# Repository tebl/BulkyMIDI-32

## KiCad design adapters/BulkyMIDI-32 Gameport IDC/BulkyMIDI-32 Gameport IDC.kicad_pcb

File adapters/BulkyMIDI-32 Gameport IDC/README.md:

# BulkyMIDI-32 Gameport (IDC)
This is an alternative version of [BulkyMIDI-32 Gameport](https://github.com/tebl/BulkyMIDI-32/tree/main/BulkyMIDI-32%20Gameport), the difference is that instead of a right-angle DB15 connector we've got an IDC connector. For more general information about what this adapter is and what it is, check out the documentation for the regular version.

Using a cable increases the cost of the unit slightly, as we'd need to buy the cable including any connectors not already on it (I've seen Uxcell-branded cables that are ready made on AliExpress and Ebay). Having the adapter on a cable means we've got the flexibility of using it mostly everywhere, primarily by not getting in the way of other inputs on the motherboard or sound card. The pinout should also match the same [pinout](https://www.frontx.com/cpx091_2.html) used on motherboard breakout cables (usually with pin 16 missing), so in theory you could use a 2x8 pin ribbon cable and connect it directly to motherboard that only has pin-headers in place of a gameport connector.

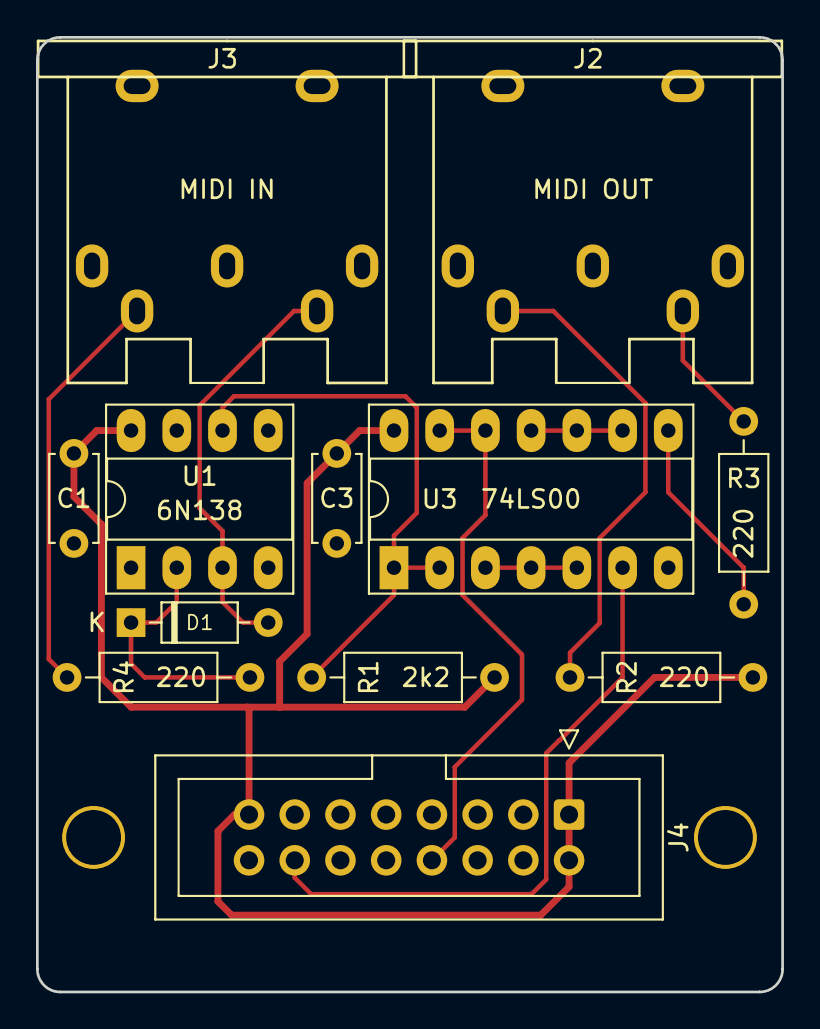
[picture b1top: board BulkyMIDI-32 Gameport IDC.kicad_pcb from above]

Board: 2 copper layers, 41.4 x 53.0 mm, 14 parts (0 on the bottom side), 13 nets.

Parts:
C1, C3: 100nF; C_Disc_D4.7mm_W2.5mm_P5.00mm
D1: 1N4148; D_DO-35_SOD27_P7.62mm_Horizontal
J2: MIDI OUT; DIN5_MIDI
J3: MIDI IN; DIN5_MIDI
J4: Gameport; Gameport_IDC
M1, M2: Mounting; M3
R1: 2k2; R_Axial_DIN0207_L6.3mm_D2.5mm_P10.16mm_Horizontal
R2, R3, R4: 220; R_Axial_DIN0207_L6.3mm_D2.5mm_P10.16mm_Horizontal
U1: 6N138; DIP-8_W7.62mm_Socket_LongPads
U3: 74LS00; DIP-14_W7.62mm_Socket_LongPads

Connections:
+5V: C1.1, C3.1, J4.1, J4.8, J4.9, R1.1, R2.1, U1.8, U3.14
GND: C1.2, C3.2, J2.2, J4.4, J4.5, U1.5, U3.7
MIDI_RxD: J4.15, U3.6
MIDI_TxD: J4.12, U3.12, U3.13
unnamed: D1.1, R4.1, U1.2
unnamed: D1.2, J3.5, U1.3
unnamed: J2.4, R2.2
unnamed: J2.5, R3.1
unnamed: J3.4, R4.2
unnamed: R1.2, U1.6, U3.1, U3.2
unnamed: R3.2, U3.8
unnamed: U3.3, U3.4, U3.5
unnamed: U3.9, U3.10, U3.11

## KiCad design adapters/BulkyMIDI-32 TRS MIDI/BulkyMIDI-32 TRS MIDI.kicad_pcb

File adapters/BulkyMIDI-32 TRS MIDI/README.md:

# BulkyMIDI-32 TRS MIDI
Working on the [BulkyMIDI-32 Internal](https://github.com/tebl/BulkyMIDI-32/tree/main/BulkyMIDI-32%20Internal) I made the choice of using TRS sockets for the MIDI-signals, thinking that was an easy way to get it connected up to my other equipment - as that would just require buying such a ready-made cable. Unfortunately though, the ones I had ordered up from China were simply wired up wrong - they were intended for audio and did not match any of the known pinouts for MIDI. I did order them up from a music store, but they've been delayed so many times that I just wanted *something* that I could rely on!

Myself. Meaning that I threw together this adapter, allowing me to use a standard 3.5mm stereo audio cable for MIDI-purposes. Yes I could probably have just ordered one from a really expensive store and have it delivered within a week from international site for professional musicians that know what they are doing, but I didn't like the fact that a short little cable - would somehow end up being the most expensive component when building an *MT32-PI*.

Helpfully enough, there are two competing standards for how such a thing should be wired - commonly referred to as *type A* and *type B*. [A simplified guide to MIDI over TRS minijacks](https://minimidi.world/) goes into all of the detail that you would ever need to understand for the both of them. In practice when it comes to the adapter that I made, there's a set of jumpers that need to be set according to the equipment you're using - either horizontal (*type A*) or vertical (*type B*).

- [1> Building the device](#1-building-the-device)
- [2> Schematic](#2-schematic)
- [3> BOM](#3-bom)

# 1> Building the device
Building the device should be a straight forward affair, you just solder the two components into place. Just don't burn yourself while doing so. Some 5-pin TRS socket types may have little plastic *"nubs"* underneath them that you may need to snip off to make it sit perfectly flush, but most will fit. 

# 2> Schematic
The supplied KiCad files should be sufficient as both a schematic and as a  starting point for ordering PCBs (basically you could just zip the contents of the export folder and upload that on a fabrication site), the schematic is also available in [PDF-format](https://github.com/tebl/BulkyMIDI-32/tree/main/documentation/schematic/adapters) and this is what you'll need to print and work your way through when things fail to work as expected.

# 3> BOM
Most parts should be easy to get a hold of from your favourite local electronic component shop, but given that I don't have access to such shops where I live so everything was based on whatever I could get cheapest from eBay/AliExpress (free shipping, but plan on waiting 3-4 weeks for delivery). 

| Reference      | Item                                                  | Count | Order  |
| ---------------| ----------------------------------------------------- | ----- | ------ |
| Faceplate PCB  | Fabricate using Gerber files                          |     1 | [PCBWay](https://www.pcbway.com/project/shareproject/MIDI_to_TRS_Adapter_fb57ed94.html)
| J1             | PJ-307 3.5mm socket (alternatively PJ-317)            |     1 |
| J2             | Female S-terminal 5pin DIN PCB                        |     1 |
| J3             | Straight pin headers, with two jumper caps            |     1 |
|                | 3.5mm TRS cable (M-M), preferably of decent quality   |     1 |

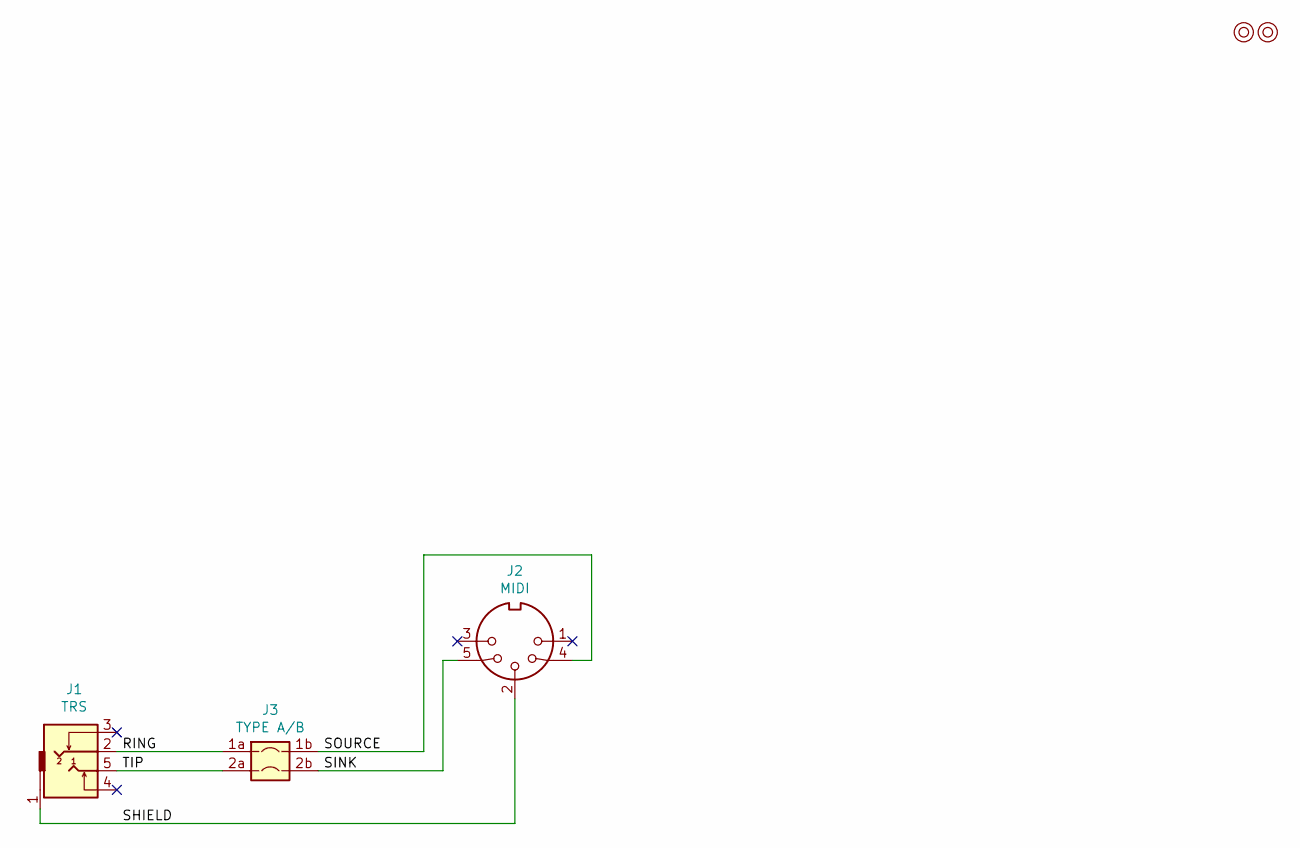
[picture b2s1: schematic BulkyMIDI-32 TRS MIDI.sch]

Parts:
J1: TRS; PJ-317
J2: MIDI; DIN5_MIDI_ANY
J3: TYPE A/B; select_swappable_THT
M1, M2: Mounting; M3

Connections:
/RING: J1.2, J3.1a
/SHIELD: J1.1, J2.2
/SINK: J2.5, J3.2b
/SOURCE: J2.4, J3.1b
/TIP: J1.5, J3.2a

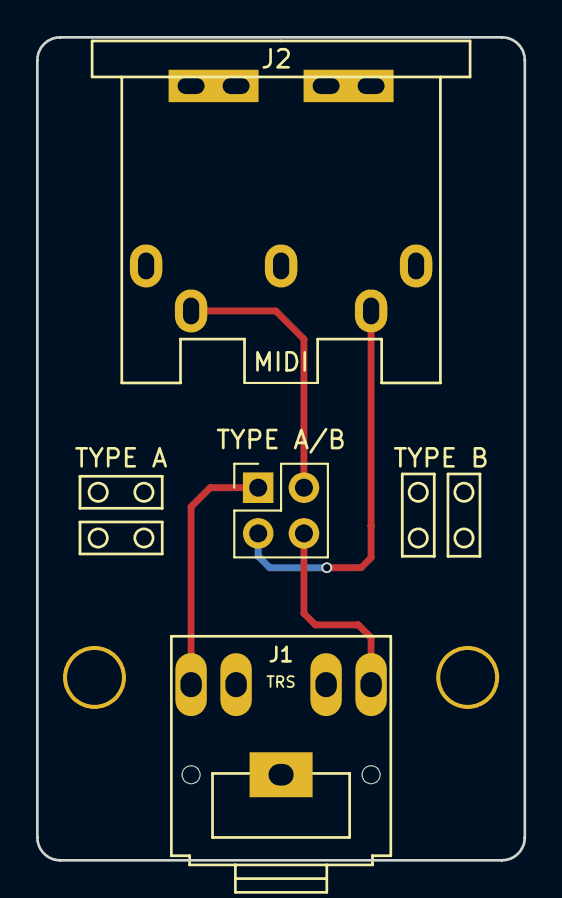
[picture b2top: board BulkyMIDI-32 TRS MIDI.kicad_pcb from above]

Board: 2 copper layers, 27.1 x 45.7 mm, 5 parts (0 on the bottom side), 5 nets.

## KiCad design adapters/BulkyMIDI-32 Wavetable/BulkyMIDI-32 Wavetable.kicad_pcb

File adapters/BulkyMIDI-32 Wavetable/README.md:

# BulkyMIDI-32 Wavetable
*UNTESTED*
While the MT32-PI already have quite a lot of options for connecting the device up to everyones favourite IBM PC/AT compatible computers, but I thought I'd put some efforts into making yet another one - this time attempting to fill the void on my **Sound Blaster 16** by having something to attach to the wavetable header.

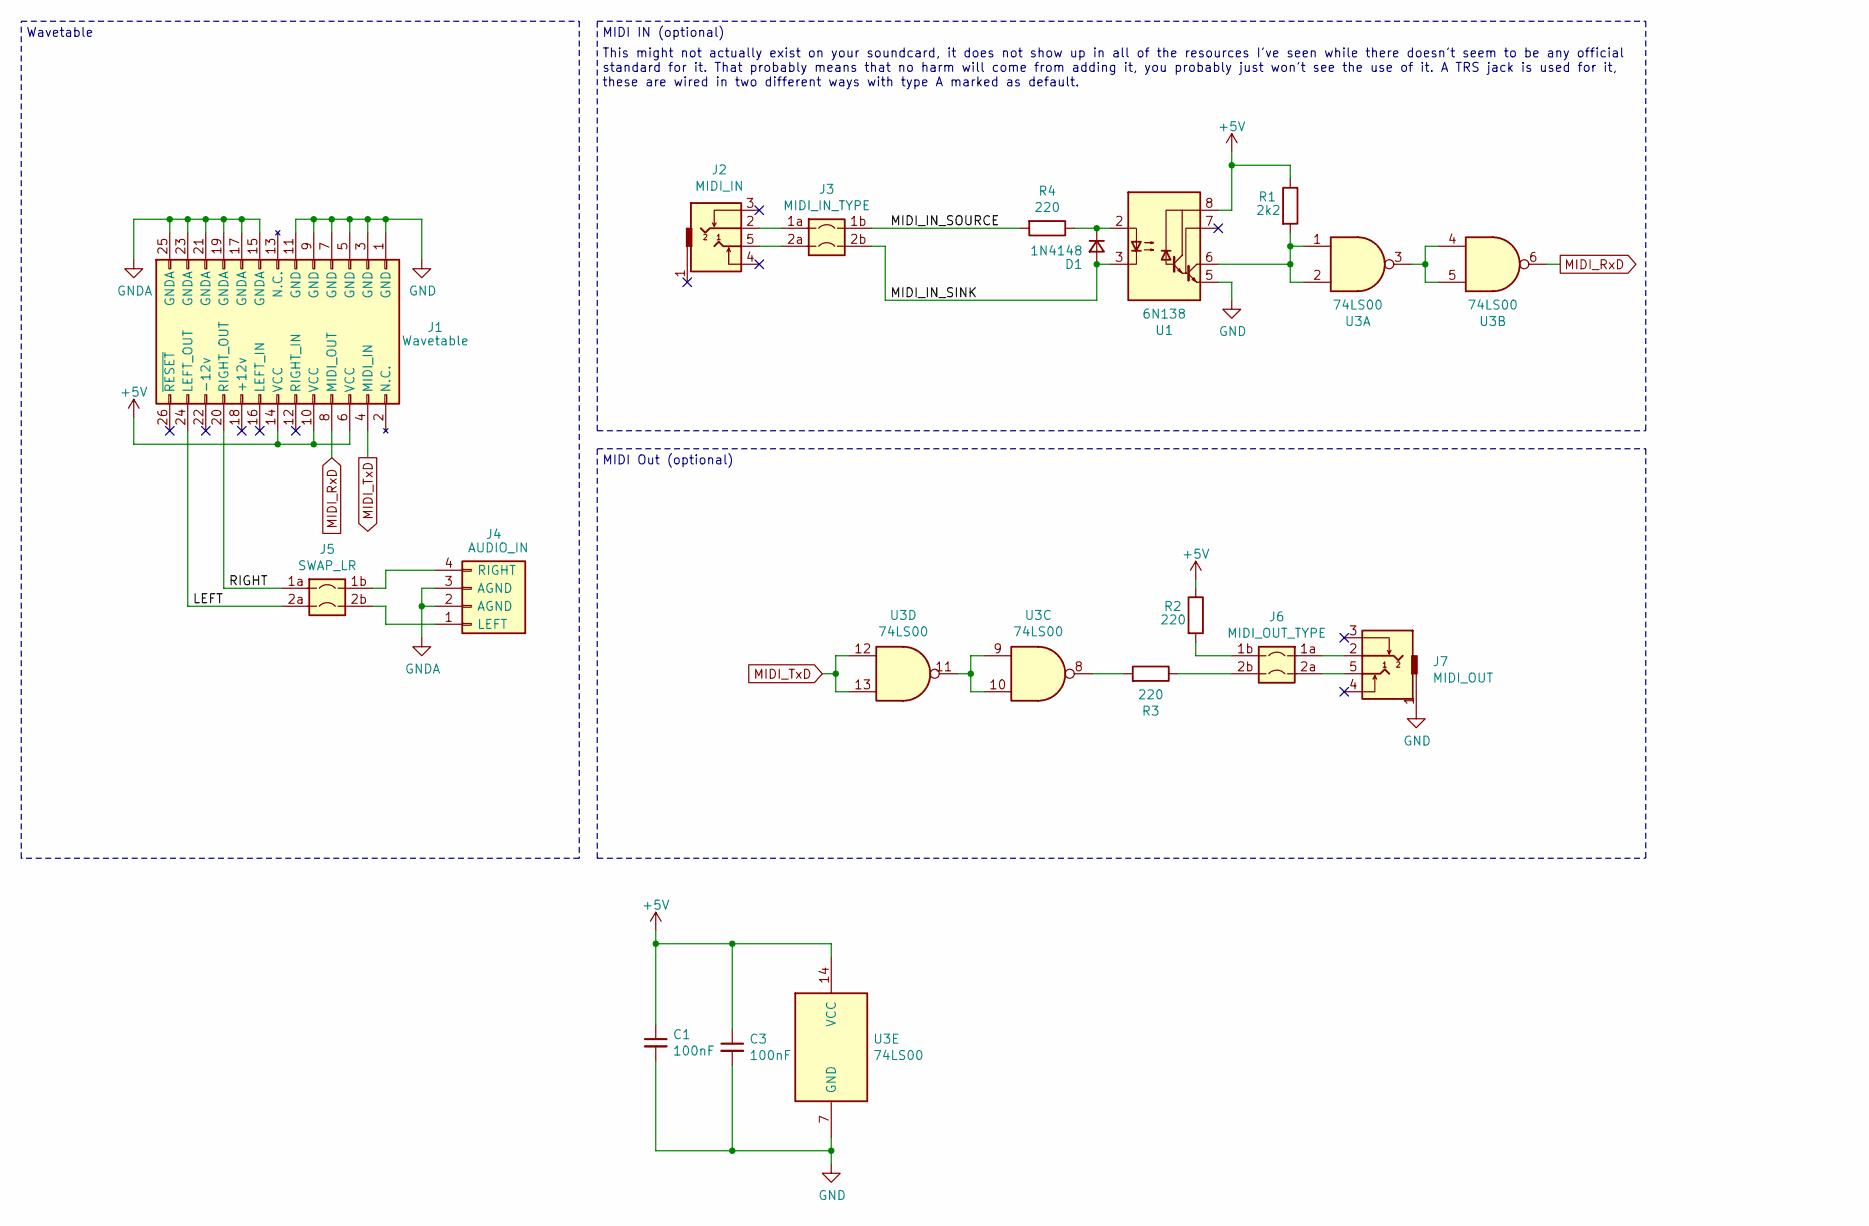
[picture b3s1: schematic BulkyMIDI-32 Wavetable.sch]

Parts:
C1, C3: 100nF; C_Disc_D4.7mm_W2.5mm_P5.00mm
D1: 1N4148; D_DO-35_SOD27_P7.62mm_Horizontal
J1: Wavetable
J2: MIDI_IN; PJ-317_IN
J3: MIDI_IN_TYPE; select_swappable
J4: AUDIO_IN; PinHeader_1x04_P2.54mm_Horizontal
J5: SWAP_LR; select_swappable
J6: MIDI_OUT_TYPE; select_swappable
J7: MIDI_OUT; PJ-317_OUT
R1: 2k2; R_Axial_DIN0207_L6.3mm_D2.5mm_P10.16mm_Horizontal
R2, R3, R4: 220; R_Axial_DIN0207_L6.3mm_D2.5mm_P10.16mm_Horizontal
U1: 6N138; DIP-8_W7.62mm_Socket_LongPads
U3: 74LS00; DIP-14_W7.62mm_Socket_LongPads

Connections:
+5V: C1.1, C3.1, J1.6 (VCC), J1.10 (VCC), J1.14 (VCC), R1.1, R2.1, U1.8 (VCC), U3.14 (VCC)
/LEFT: J1.24 (LEFT_OUT), J5.2a
/MIDI_IN_SINK: D1.2 (A), J3.2b, U1.3 (C2)
/MIDI_IN_SOURCE: J3.1b, R4.2
/RIGHT: J1.20 (RIGHT_OUT), J5.1a
GND: C1.2, C3.2, J1.1 (GND), J1.3 (GND), J1.5 (GND), J1.7 (GND), J1.9 (GND), J1.11 (GND), J7.1, U1.5 (GND), U3.7 (GND)
GNDA: J1.15 (GNDA), J1.17 (GNDA), J1.19 (GNDA), J1.21 (GNDA), J1.23 (GNDA), J1.25 (GNDA), J4.2 (AGND), J4.3 (AGND)
MIDI_RxD: J1.8 (MIDI_OUT), U3.6
MIDI_TxD: J1.4 (MIDI_IN), U3.12, U3.13
unnamed: D1.1 (K), R4.1, U1.2 (C1)
unnamed: J2.2, J3.1a
unnamed: J2.5, J3.2a
unnamed: J4.1 (LEFT), J5.2b
unnamed: J4.4 (RIGHT), J5.1b
unnamed: J6.1a, J7.2
unnamed: J6.1b, R2.2
unnamed: J6.2a, J7.5
unnamed: J6.2b, R3.1
unnamed: R1.2, U1.6 (VO2), U3.1, U3.2
unnamed: R3.2, U3.8
unnamed: U3.3, U3.4, U3.5
unnamed: U3.9, U3.10, U3.11

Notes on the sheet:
MIDI IN (optional)
MIDI Out (optional)
Wavetable
This might not actually exist on your soundcard, it does not show up in all of the resources I've seen while there doesn't seem to be any official standard for it. That probably means that no harm will come from adding it, you probably just won't see the use of it. A TRS jack is used for it, these 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

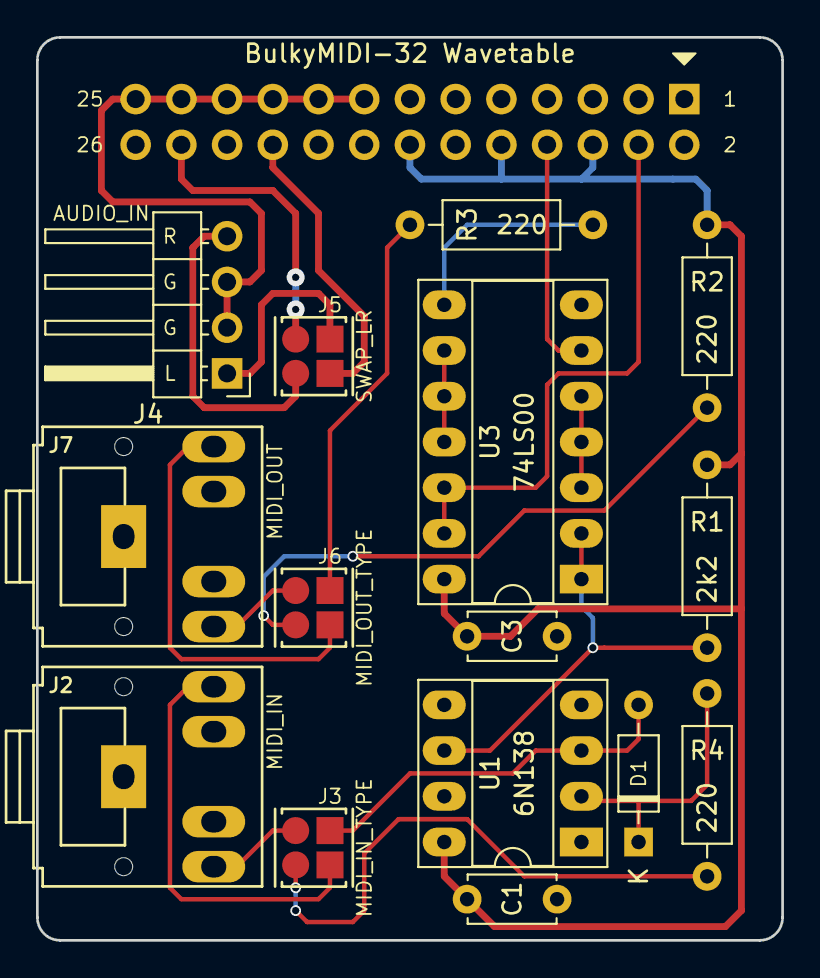
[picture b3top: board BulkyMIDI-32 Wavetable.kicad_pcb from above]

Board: 2 copper layers, 41.4 x 50.2 mm, 16 parts (0 on the bottom side), 22 nets.

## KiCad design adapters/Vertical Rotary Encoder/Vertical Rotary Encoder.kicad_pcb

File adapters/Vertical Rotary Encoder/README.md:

# Vertical Rotary Encoder
**NB!** This board was only used with the first versions of the BulkyMIDI-32, if you have one where the display is in the middle then this is not needed. This is because the functionality was replaced when I found the room to add a front-facing panel to it.

While designing the BulkyMIDI-32 I looked hard and long at locating a suitable part for a rotary encoder meant to mount at an angle, but while there were references to them existing at some point in time they do not seem to be available - at least not at a price I was prepared to pay for it. Originally I had wanted to use one of the common rotary encoder modules such as the well known *KY-040* that's being sold by the same vendors dealing in Arduino-modules in general.

One problem with simply buying these modules, is that the PCB that they come mounted on is simply too large to use within a device as small as the BulkyMIDI-32 (not that it's really *that* small to be honest). The solution I as all things tend to become once KiCAD is already installed, is to just design a small adapter board that'll fit our purposes. Using commonly available *EC11 Rotary Encoder*, essentially the thing that comes installed on the already mentioned modules. At first glance the tabs on the top and bottom might look a bit odd, but they slot into the other modules - adding mechanical strength to what would ordinarily be a weak spot.

- [1> Building the device](#1-building-the-device)
- [2> Schematic](#2-schematic)
- [3> BOM](#3-bom)

# 1> Building the device
Building the device should be a straight forward affair, you just solder the two components into place. Pay attention to keep the alignment somewhat straight, in particular the right-angle pin header needs to be flush against the board.

It has two solder jumpers on the back where you'd usually link pins 1-2 in normal operation, pin 1 indicated by the small triangle. If you find that the rotary encoder moves backwards from what you'd expect without a way in software to change it, change the jumpers so that they link pins 2-3.

# 2> Schematic
The supplied KiCad files should be sufficient as both a schematic and as a  starting point for ordering PCBs (basically you could just zip the contents of the export folder and upload that on a fabrication site), the schematic is also available in [PDF-format](https://github.com/tebl/BulkyMIDI-32/tree/main/documentation/schematic/adapters) and this is what you'll need to print and work your way through when things fail to work as expected.

# 3> BOM
Most parts should be easy to get a hold of from your favourite local electronic component shop, but given that I don't have access to such shops where I live so everything was based on whatever I could get cheapest from eBay/AliExpress (free shipping, but plan on waiting 3-4 weeks for delivery). 

| Reference      | Item                                                  | Count | Order  |
| ---------------| ----------------------------------------------------- | ----- | ------ |
| Faceplate PCB  | Fabricate using Gerber files                          |     1 | [PCBWay](https://www.pcbway.com/project/shareproject/BulkyMIDI_32_Vertical_Rotary_Encoder_352faf4d.html)
| ENC1           | EC11 rotary encoder, 20mm. Preferably plum handle     |     1 |
| J1             | 4-pin segment of right-angle pin header               |     1 |

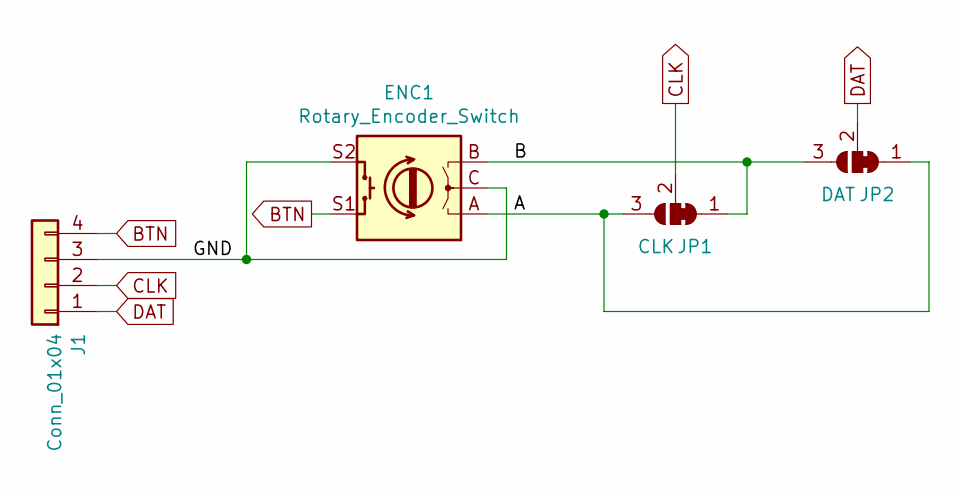
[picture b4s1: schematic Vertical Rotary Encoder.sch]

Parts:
ENC1: Rotary_Encoder_Switch; RotaryEncoder_Alps_EC11E-Switch_Vertical_H20mm
J1: Conn_01x04; PinHeader_1x04_P2.54mm_Horizontal
JP1: CLK; SolderJumper-3_P1.3mm_Open_Pad1.0x1.5mm
JP2: DAT; SolderJumper-3_P1.3mm_Open_Pad1.0x1.5mm

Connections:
/A: ENC1.A, JP1.3 (B), JP2.1 (A)
/B: ENC1.B, JP1.1 (A), JP2.3 (B)
/GND: ENC1.C, ENC1.S2, J1.3
BTN: ENC1.S1, J1.4
CLK: J1.2, JP1.2 (C)
DAT: J1.1, JP2.2 (C)

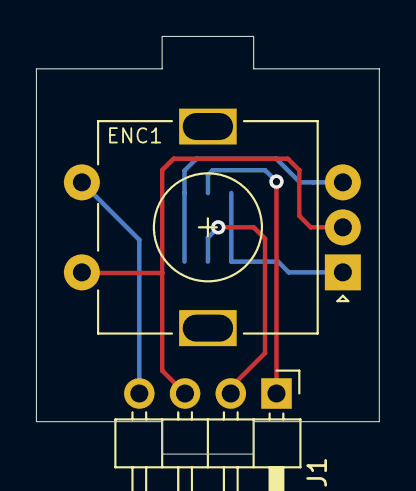
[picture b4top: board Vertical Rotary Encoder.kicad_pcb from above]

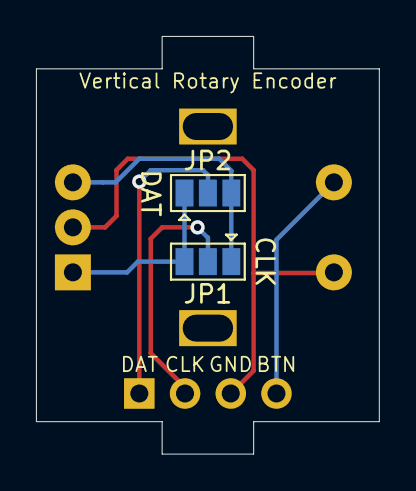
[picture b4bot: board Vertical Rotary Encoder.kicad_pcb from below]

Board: 2 copper layers, 19.1 x 23.2 mm, 4 parts (2 on the bottom side), 6 nets.
